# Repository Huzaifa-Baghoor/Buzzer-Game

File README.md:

# Buzzer Game

This is a buzzer game setup like we see in TV shows, in which the player that presses the button first, his buzzer beeps and all other players are locked out until the admin allows.

## Working

The 74HC373 IC has an octal D-Latch that controls the first to press logic. The LE pin is controlled by a feedback loop. When a player presses his button the IC captures that state by pulling the LE pin low and freezes the mechanism and when the admin button is pressed it resets the latch.

## PCB

I made a PCB for this project, I tried to keep it single sided but there are two tracks that are on the bottom layer.

|Schematics|Tracks|
| :---: | :---: |
|  |  |

## 3D Casing

I also designed a 3D enclosure box for the Project.

|Box|Lid|
| :---: | :---: |
|  |  |

## Bill of Materials (BOM)

| Name | Quantity | Total Cost (USD) | Link | Distributor |
| :---: | :---: | :---: | :---: | :---: |
| Solder Mask | 1 | 1.65 | [Solder Mask](https://epro.pk/product/10cc-uv-solder-mask-ink-flux-welding-mechanic-in-pakistan/) | EPro |
| Ferric Chloride | 2 | 1.00 | [Ferric Chloride](https://epro.pk/product/ferric-chloride-powder-for-pcb-etchant-fecl-in-pakistan/) | EPro |
| Rivets | 1 | 9.00 | - | AliExpress |
| Transparency Sheets | 1 | 8.00 | [Transparency Sheets](https://stationers.pk/products/transparency-sheets?_pos=1&_sid=1455f1e48&_ss=r) | Stationers |
| Copper Clad Board | 1 | 7.00 | [Copper Clad Board](https://epro.pk/product/double-sided-pcb-12x12-in-pakistan/) | EPro |
| Reflow Gun | 1 | 15.00 | [Reflow Gun](https://digilog.pk/products/kada-835d-hot-air-gun-smd-rework-station-thermo-control-anti-static-portable-smd-rework-station) | DigiLog |
| Resistors | 11 | 4.86 | [Resistors](https://www.aliexpress.com/item/1005004145810949.html?spm=a2g0o.cart.0.0.1a3438dapWXx8H&mp=1&pdp_npi=6%40dis%21USD%21USD+1.62%21USD+1.61%21%21USD+1.61%21%21%21%402141122217765785921945522e1a32%2112000028184503888%21ct%21PK%212961473668%21%211%210%21) | AliExpress |
| Buzzer | 3 | 4.36 | [Buzzer](https://www.aliexpress.com/item/4000043951008.html?spm=a2g0o.cart.0.0.1a3438daAFLFTm&mp=1&pdp_npi=6%40dis%21USD%21USD+2.18%21USD+2.18%21%21USD+2.18%21%21%21%402140c1e917765782907343521ed3bd%2110000000099604494%21ct%21PK%212961473668%21%211%210%21&pdp_ext_f=%7B%22cart2PdpParams%22%3A%7B%22pdpBusinessMode%22%3A%22retail%22%7D%7D) | AliExpress |
| LEDs | 3 | 7.00 | [LEDs](https://www.aliexpress.com/item/1005009128722843.html?spm=a2g0o.cart.0.0.1a3438daAFLFTm&mp=1&pdp_npi=6%40dis%21USD%21USD+2.21%21USD+2.21%21%21USD+2.21%21%21%21%402140c1e917765782907343521ed3bd%2112000048016234041%21ct%21PK%212961473668%21%211%210%21) | AliExpress |
| Button | 4 | 1.59 | [Button](https://www.aliexpress.com/item/1005001304127863.html?spm=a2g0o.cart.0.0.1a3438daAFLFTm&mp=1&pdp_npi=6%40dis%21USD%21USD+1.70%21USD+1.68%21%21USD+1.68%21%21%21%402140c1e917765782907343521ed3bd%2112000015639874024%21ct%21PK%212961473668%21%211%210%21) | AliExpress |
| 1N4007 Diode | 3 | 2.38 | [Diode](https://www.aliexpress.com/item/32751841595.html?spm=a2g0o.cart.0.0.1a3438daAFLFTm&mp=1&pdp_npi=6%40dis%21USD%21USD+2.32%21USD+2.32%21%21USD+2.20%21%21%21%402140c1e917765782907343521ed3bd%2112000016561662489%21ct%21PK%212961473668%21%211%210%21) | AliExpress |
| BC847 Transistor | 2 | 2.32 | [Transistor](https://www.aliexpress.com/item/1005008829335370.html?spm=a2g0o.cart.0.0.1a3438daAFLFTm&mp=1&pdp_npi=6%40dis%21USD%21USD+2.44%21USD+2.37%21%21USD+2.37%21%21%21%402140c1e917765782498232725ed3bd%2112000046856587364%21ct%21PK%212961473668%21%211%210%21) | AliExpress |
| 74HC373 IC | 1 | 4.11 | [74HC373 IC](https://www.aliexpress.com/item/33052702425.html?spm=a2g0o.cart.0.0.1a3438daAFLFTm&mp=1&pdp_npi=6%40dis%21USD%21USD+4.11%21USD+4.11%21%21USD+4.03%21%21%21%402140c1e917765782778963273ed3bd%2167402727853%21ct%21PK%212961473668%21%211%210%21&pdp_ext_f=%7B%22cart2PdpParams%22%3A%7B%22pdpBusinessMode%22%3A%22retail%22%7D%7D) | AliExpress |

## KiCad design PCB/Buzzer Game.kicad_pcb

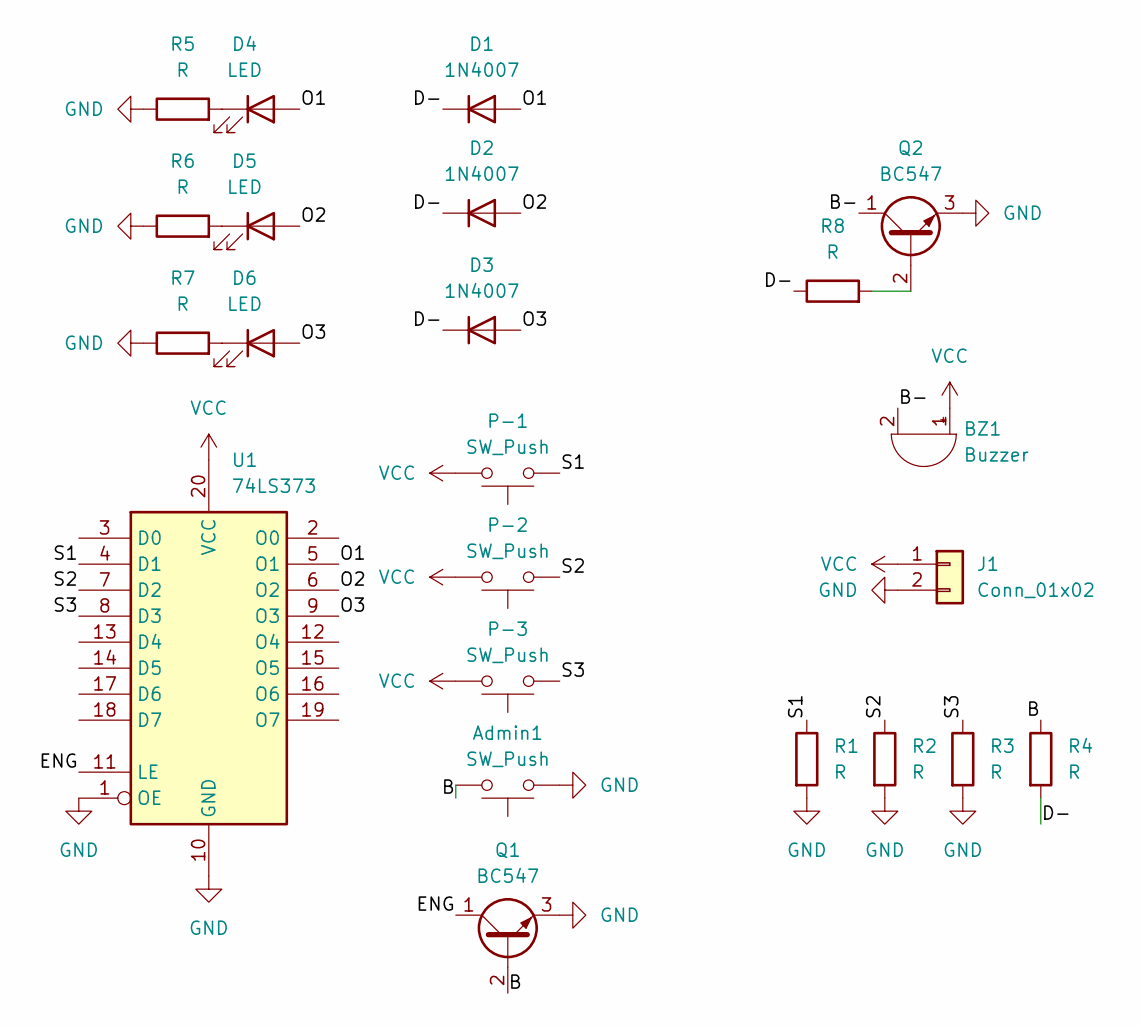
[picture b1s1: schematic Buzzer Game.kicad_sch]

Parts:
Admin1: SW_Push; SW_PUSH_6mm
BZ1: Buzzer; Buzzer_12x9.5RM7.6
D1, D2, D3: 1N4007; D_DO-41_SOD81_P10.16mm_Horizontal
D4, D5, D6: LED; LED_D5.0mm
J1: Conn_01x02; TerminalBlock_Phoenix_MKDS-1,5-2-5.08_1x02_P5.08mm_Horizont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
P-1, P-2, P-3: SW_Push; SW_PUSH_6mm
Q1, Q2: BC547; TO-92_Inline
R1, R2, R3, R4, R5, R6, R7, R8: R; R_Axial_DIN0207_L6.3mm_D2.5mm_P10.16mm_Horizontal
U1: 74LS373; DIP-20_W7.62mm_LongPads

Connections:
/B: Admin1.2, Q1.2 (B), R4.1
/B-: BZ1.2 (-), Q2.1 (C)
/D-: D1.1 (K), D2.1 (K), D3.1 (K), R4.2, R8.1
/ENG: Q1.1 (C), U1.11 (LE)
/O1: D1.2 (A), D4.2 (A), U1.5 (O1)
/O2: D2.2 (A), D5.2 (A), U1.6 (O2)
/O3: D3.2 (A), D6.2 (A), U1.9 (O3)
/S1: P-1.1, R1.1, U1.4 (D1)
/S2: P-2.1, R2.1, U1.7 (D2)
/S3: P-3.1, R3.1, U1.8 (D3)
GND: Admin1.1, J1.2, Q1.3 (E), Q2.3 (E), R1.2, R2.2, R3.2, R5.1, R6.1, R7.1, U1.1 (OE), U1.10 (GND)
unnamed: D4.1 (K), R5.2
unnamed: D5.1 (K), R6.2
unnamed: D6.1 (K), R7.2
unnamed: Q2.2 (B), R8.2
VCC: BZ1.1 (+), J1.1, P-1.2, P-2.2, P-3.2, U1.20 (VCC)

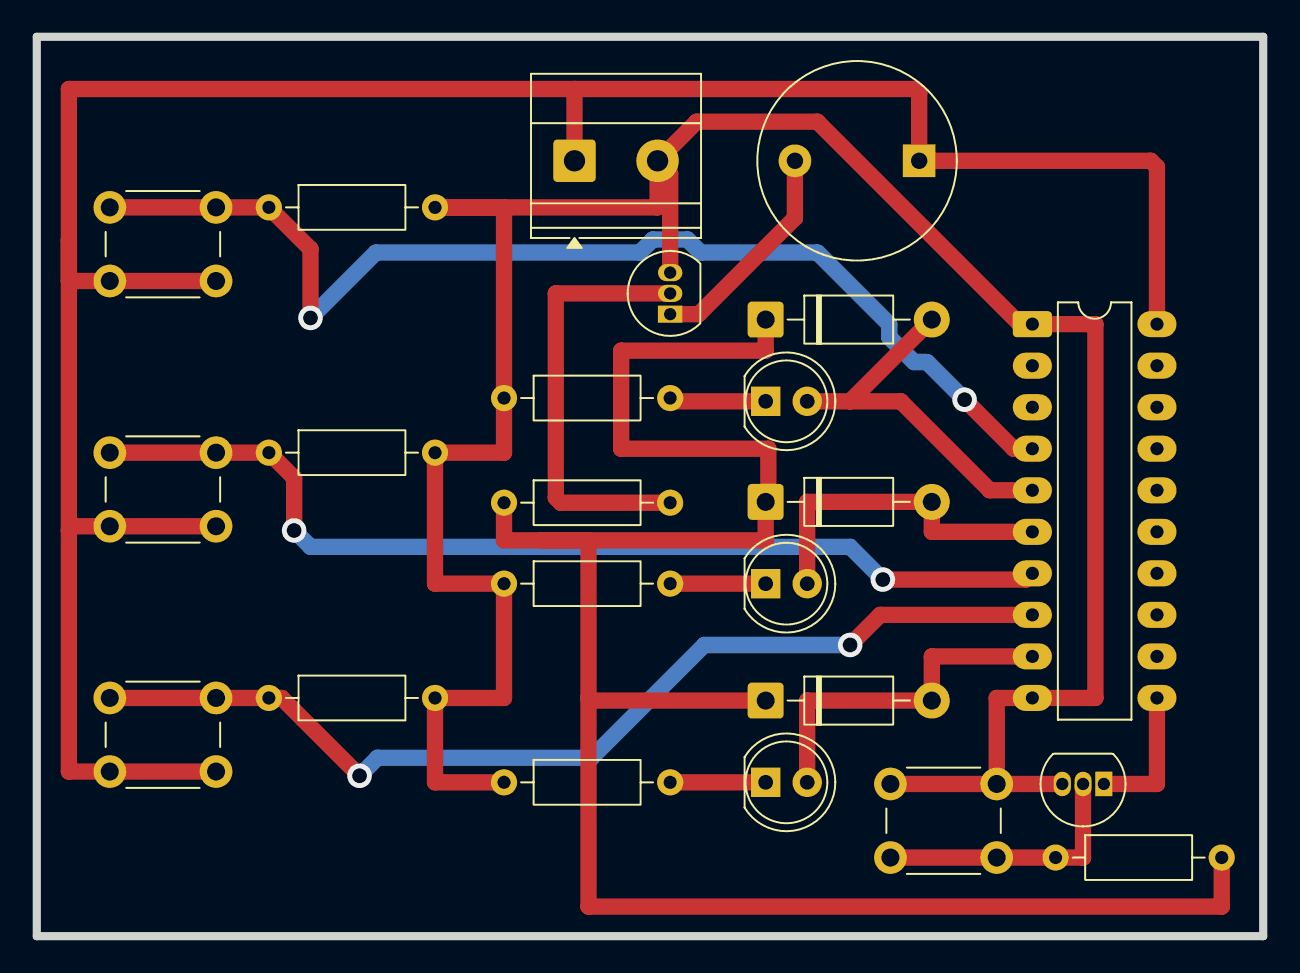
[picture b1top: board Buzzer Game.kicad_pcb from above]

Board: 2 copper layers, 75.0 x 55.0 mm, 23 parts (0 on the bottom side), 16 nets.

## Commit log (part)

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2026-04-19 PCB and 3D files
2026-04-19 Made README.md File
2026-04-26 BOM added
2026-04-30 BOM.csv
2026-04-30 Updated README.md according to BOM.csv
2026-04-30 Organized Repo
2026-05-02 3D Assembly
